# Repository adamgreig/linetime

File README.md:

# Linetime

Measure the line time. As precisely and accurately as feasible.

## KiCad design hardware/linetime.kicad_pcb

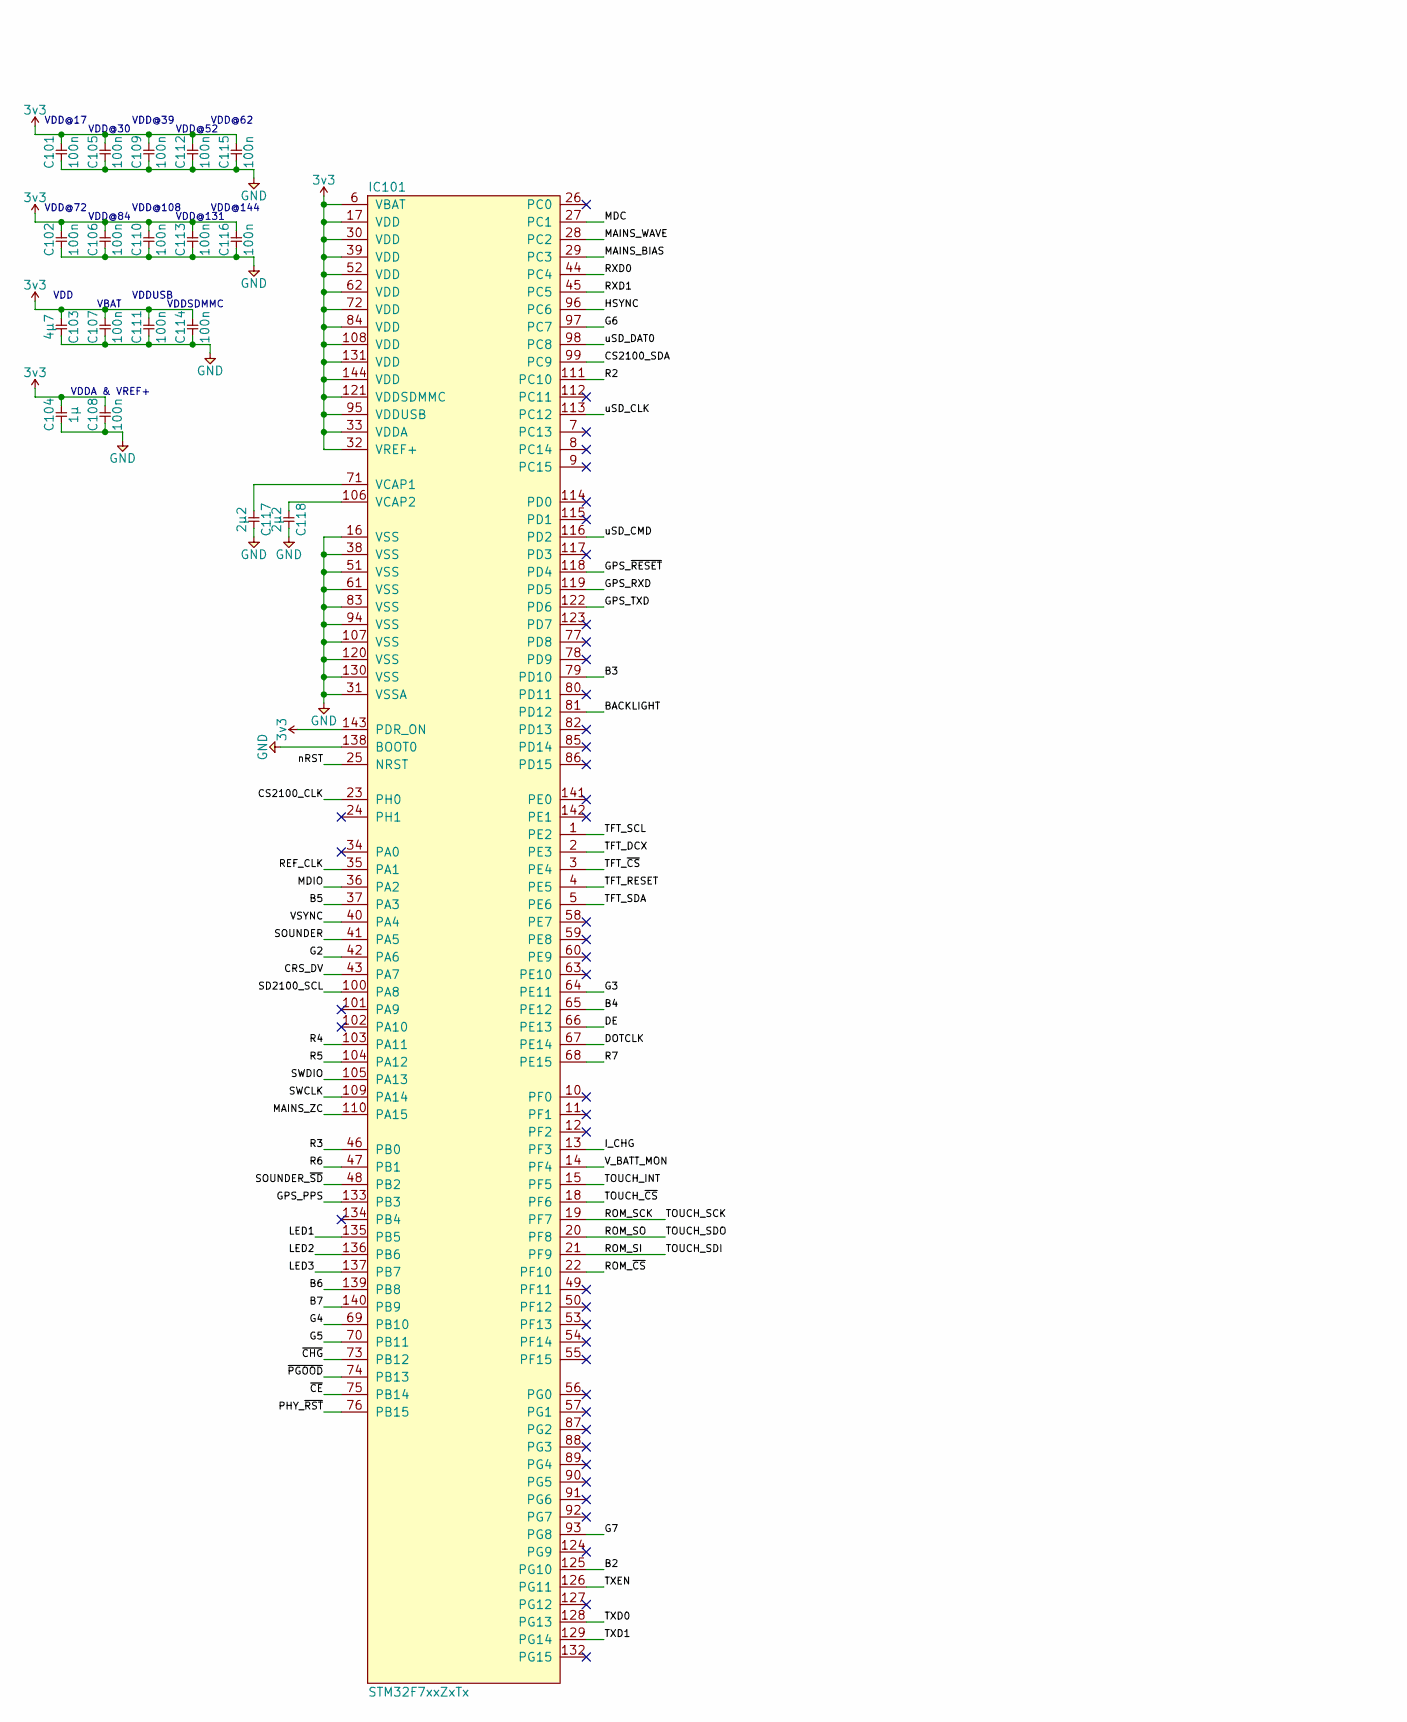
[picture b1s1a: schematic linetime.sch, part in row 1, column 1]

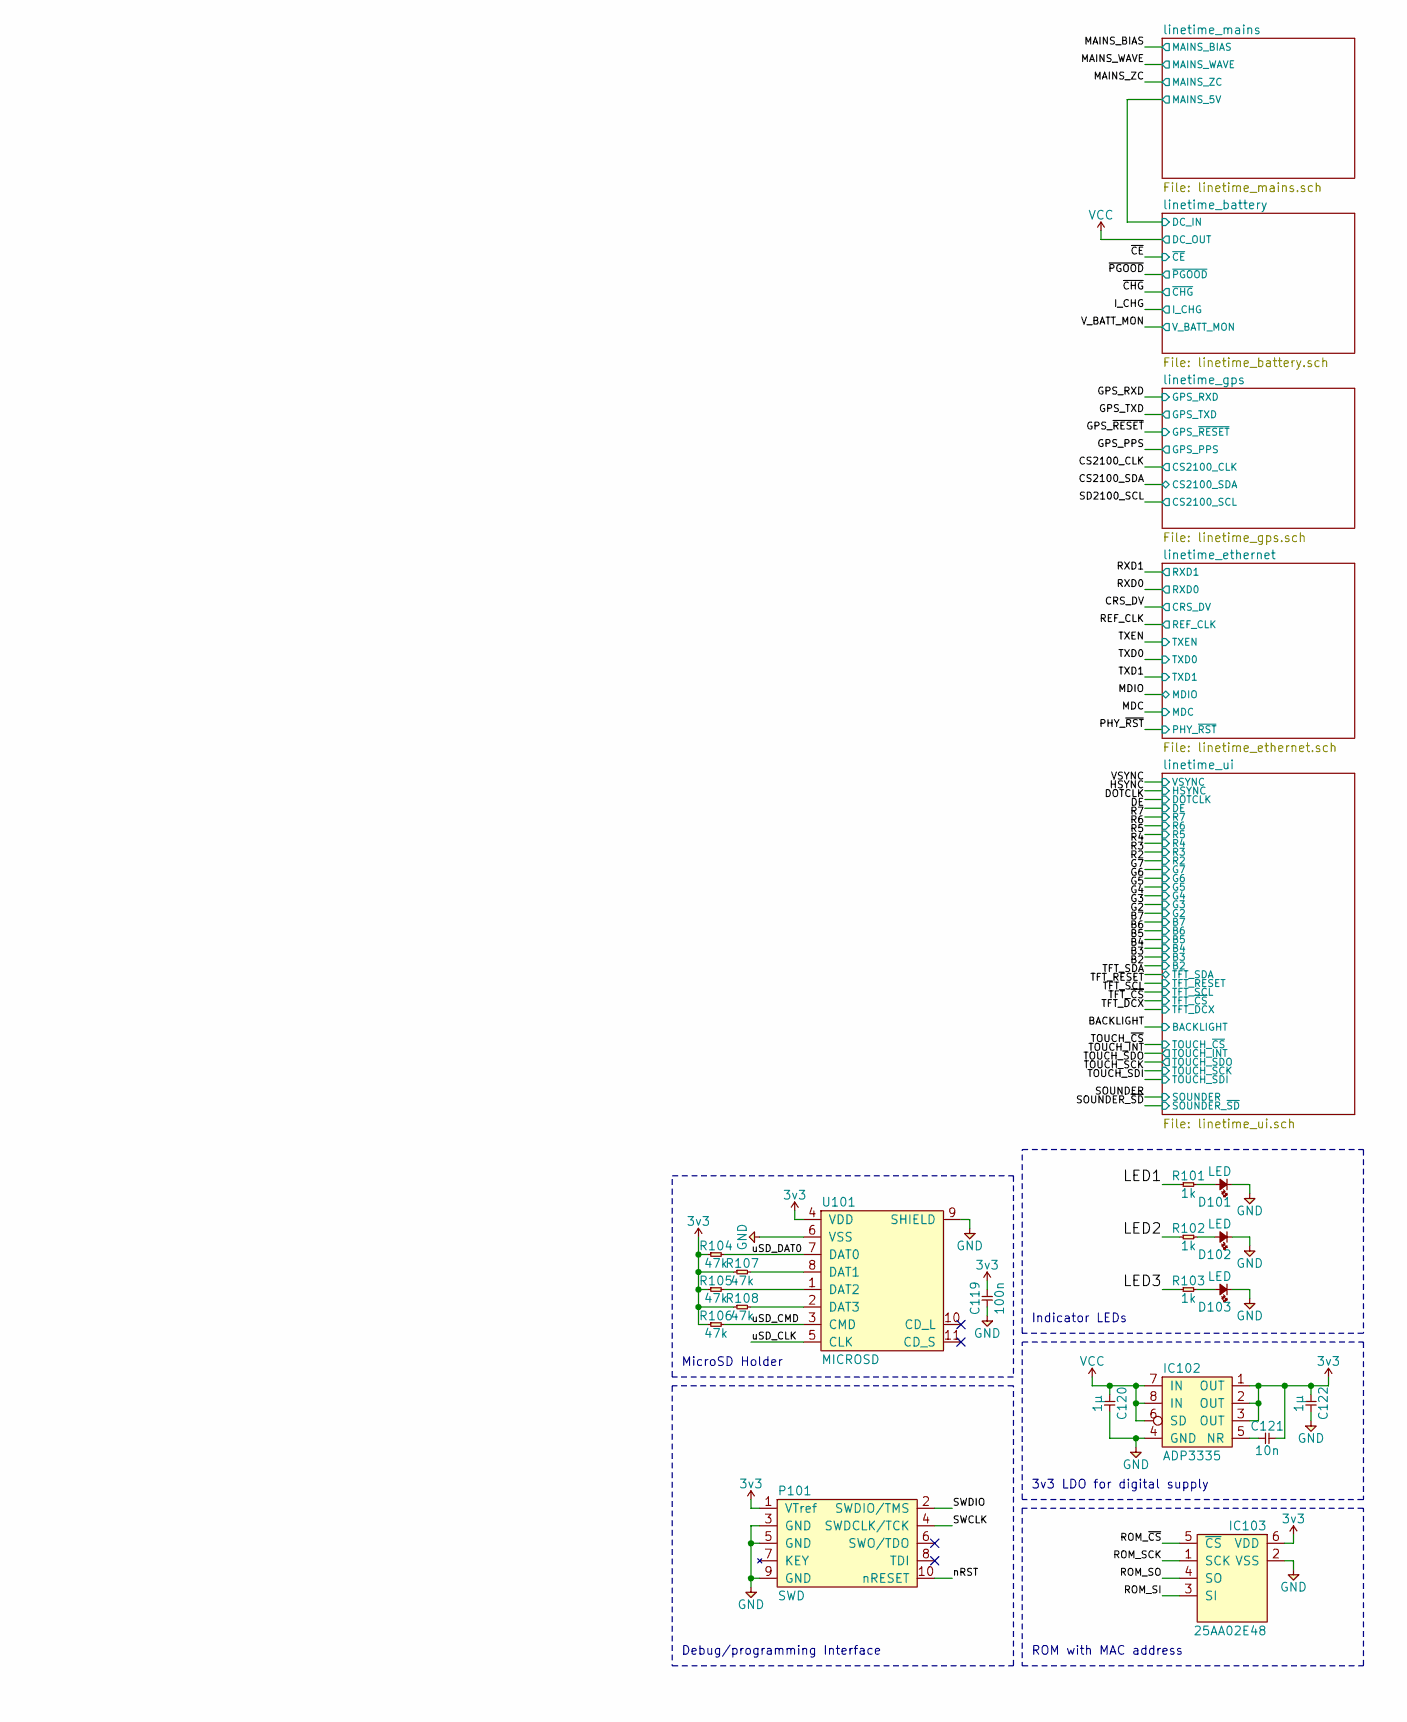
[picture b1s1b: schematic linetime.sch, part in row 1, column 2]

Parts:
C101, C102, C105, C106, C107, C108, C109, C110, C111, C112, C113, C114, C115, C116, C119: 100n; 0603
C103: 4µ7; 0603
C104, C120, C122: 1µ; 0603
C117, C118: 2µ2; 0603
C121: 10n; 0603
D101, D102, D103: LED; 0603-LED
IC101: STM32F7xxZxTx; LQFP-144; Farnell 2535499
IC102: ADP3335; MSOP-8; Farnell 2067775
IC103: 25AA02E48; SOT-23-6; Farnell 1700995
P101: SWD; FTSH-105-01-F-D-K
R101, R102, R103: 1k; 0603
R104, R105, R106, R107, R108: 47k; 0603
U101: MICROSD; MICROSD_MOLEX_503398-1892; Farnell 2358234

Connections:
3v3: C101.1, C102.1, C103.1, C104.1, C105.1, C106.1, C107.1, C108.1, C109.1, C110.1, C111.1, C112.1, C113.1, C114.1, C115.1, C116.1, C119.1, C121.2, C122.1, IC101.6 (VBAT), IC101.17 (VDD), IC101.30 (VDD), IC101.32 (VREF+), IC101.33 (VDDA), IC101.39 (VDD), IC101.52 (VDD), IC101.62 (VDD), IC101.72 (VDD), IC101.84 (VDD), IC101.95 (VDDUSB), IC101.108 (VDD), IC101.121 (VDDSDMMC), IC101.131 (VDD), IC101.143 (PDR_ON), IC101.144 (VDD), IC102.1 (OUT), IC102.2 (OUT), IC102.3 (OUT), IC103.6 (VDD), P101.1 (VTref), R104.1, R105.1, R106.1, R107.1, R108.1, U101.4 (VDD); also elsewhere on the board
/B2: IC101.125 (PG10); also elsewhere on the board
/B3: IC101.79 (PD10); also elsewhere on the board
/B4: IC101.65 (PE12); also elsewhere on the board
/B5: IC101.37 (PA3); also elsewhere on the board
/B6: IC101.139 (PB8); also elsewhere on the board
/B7: IC101.140 (PB9); also elsewhere on the board
/BACKLIGHT: IC101.81 (PD12); also elsewhere on the board
/CRS_DV: IC101.43 (PA7); also elsewhere on the board
/CS2100_CLK: IC101.23 (PH0); also elsewhere on the board
/CS2100_SDA: IC101.99 (PC9); also elsewhere on the board
/DE: IC101.66 (PE13); also elsewhere on the board
/DOTCLK: IC101.67 (PE14); also elsewhere on the board
/G2: IC101.42 (PA6); also elsewhere on the board
/G3: IC101.64 (PE11); also elsewhere on the board
/G4: IC101.69 (PB10); also elsewhere on the board
/G5: IC101.70 (PB11); also elsewhere on the board
/G6: IC101.97 (PC7); also elsewhere on the board
/G7: IC101.93 (PG8); also elsewhere on the board
/GPS_PPS: IC101.133 (PB3); also elsewhere on the board
/GPS_RXD: IC101.119 (PD5); also elsewhere on the board
/GPS_TXD: IC101.122 (PD6); also elsewhere on the board
/GPS_~RESET: IC101.118 (PD4); also elsewhere on the board
/HSYNC: IC101.96 (PC6); also elsewhere on the board
/I_CHG: IC101.13 (PF3); also elsewhere on the board
/LED1: IC101.135 (PB5), R101.1
/LED2: IC101.136 (PB6), R102.1
/LED3: IC101.137 (PB7), R103.1
/MAINS_BIAS: IC101.29 (PC3); also elsewhere on the board
/MAINS_WAVE: IC101.28 (PC2); also elsewhere on the board
/MAINS_ZC: IC101.110 (PA15); also elsewhere on the board
/MDC: IC101.27 (PC1); also elsewhere on the board
/MDIO: IC101.36 (PA2); also elsewhere on the board
/PHY_~RST: IC101.76 (PB15); also elsewhere on the board
/R2: IC101.111 (PC10); also elsewhere on the board
/R3: IC101.46 (PB0); also elsewhere on the board
/R4: IC101.103 (PA11); also elsewhere on the board
/R5: IC101.104 (PA12); also elsewhere on the board
/R6: IC101.47 (PB1); also elsewhere on the board
/R7: IC101.68 (PE15); also elsewhere on the board
/REF_CLK: IC101.35 (PA1); also elsewhere on the board
/ROM_SCK: IC101.19 (PF7), IC103.1 (SCK); also elsewhere on the board
/ROM_SI: IC101.21 (PF9), IC103.3 (SI); also elsewhere on the board
/ROM_SO: IC101.20 (PF8), IC103.4 (SO); also elsewhere on the board
/ROM_~CS: IC101.22 (PF10), IC103.5 (~CS)
/RXD0: IC101.44 (PC4); also elsewhere on the board
/RXD1: IC101.45 (PC5); also elsewhere on the board
/SD2100_SCL: IC101.100 (PA8); also elsewhere on the board
/SOUNDER: IC101.41 (PA5); also elsewhere on the board
/SOUNDER_~SD: IC101.48 (PB2); also elsewhere on the board
/SWCLK: IC101.109 (PA14), P101.4 (SWDCLK/TCK)
/SWDIO: IC101.105 (PA13), P101.2 (SWDIO/TMS)
/TFT_DCX: IC101.2 (PE3); also elsewhere on the board
/TFT_RESET: IC101.4 (PE5); also elsewhere on the board
/TFT_SCL: IC101.1 (PE2); also elsewhere on the board
/TFT_SDA: IC101.5 (PE6); also elsewhere on the board
/TFT_~CS: IC101.3 (PE4); also elsewhere on the board
/TOUCH_INT: IC101.15 (PF5); also elsewhere on the board
/TOUCH_~CS: IC101.18 (PF6); also elsewhere on the board
/TXD0: IC101.128 (PG13); also elsewhere on the board
/TXD1: IC101.129 (PG14); also elsewhere on the board
/TXEN: IC101.126 (PG11); also elsewhere on the board
/VSYNC: IC101.40 (PA4); also elsewhere on the board
/V_BATT_MON: IC101.14 (PF4); also elsewhere on the board
/nRST: IC101.25 (NRST), P101.10 (nRESET)
/uSD_CLK: IC101.113 (PC12), U101.5 (CLK)
/uSD_CMD: IC101.116 (PD2), R106.2, U101.3 (CMD)
/uSD_DAT0: IC101.98 (PC8), R104.2, U101.7 (DAT0)
/~CE: IC101.75 (PB14); also elsewhere on the board
/~CHG: IC101.73 (PB12); also elsewhere on the board
/~PGOOD: IC101.74 (PB13); also elsewhere on the board
GND: C101.2, C102.2, C103.2, C104.2, C105.2, C106.2, C107.2, C108.2, C109.2, C110.2, C111.2, C112.2, C113.2, C114.2, C115.2, C116.2, C117.2, C118.2, C119.2, C120.2, C122.2, D101.1, D102.1, D103.1, IC101.16 (VSS), IC101.31 (VSSA), IC101.38 (VSS), IC101.51 (VSS), IC101.61 (VSS), IC101.83 (VSS), IC101.94 (VSS), IC101.107 (VSS), IC101.120 (VSS), IC101.130 (VSS), IC101.138 (BOOT0), IC102.4 (GND), IC103.2 (VSS), P101.3 (GND), P101.5 (GND), P101.9 (GND), U101.6 (VSS), U101.9 (SHIELD); also elsewhere on the board
unnamed: C117.1, IC101.71 (VCAP1)
unnamed: C118.1, IC101.106 (VCAP2)
unnamed: C121.1, IC102.5 (NR)
unnamed: D101.2, R101.2
unnamed: D102.2, R102.2
unnamed: D103.2, R103.2
unnamed: R105.2, U101.1 (DAT2)
unnamed: R107.2, U101.8 (DAT1)
unnamed: R108.2, U101.2 (DAT3)
VCC: C120.1, IC102.6 (SD), IC102.7 (IN), IC102.8 (IN); also elsewhere on the board

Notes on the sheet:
3v3 LDO for digital supply
ROM with MAC address
MicroSD Holder
Debug/programming Interface
VDDA & VREF+
VDDUSB
VDDSDMMC
VBAT
VDD
VDD@17
VDD@30
VDD@39
VDD@52
VDD@62
VDD@72
VDD@84
VDD@108
VDD@131
VDD@144
Indicator LEDs

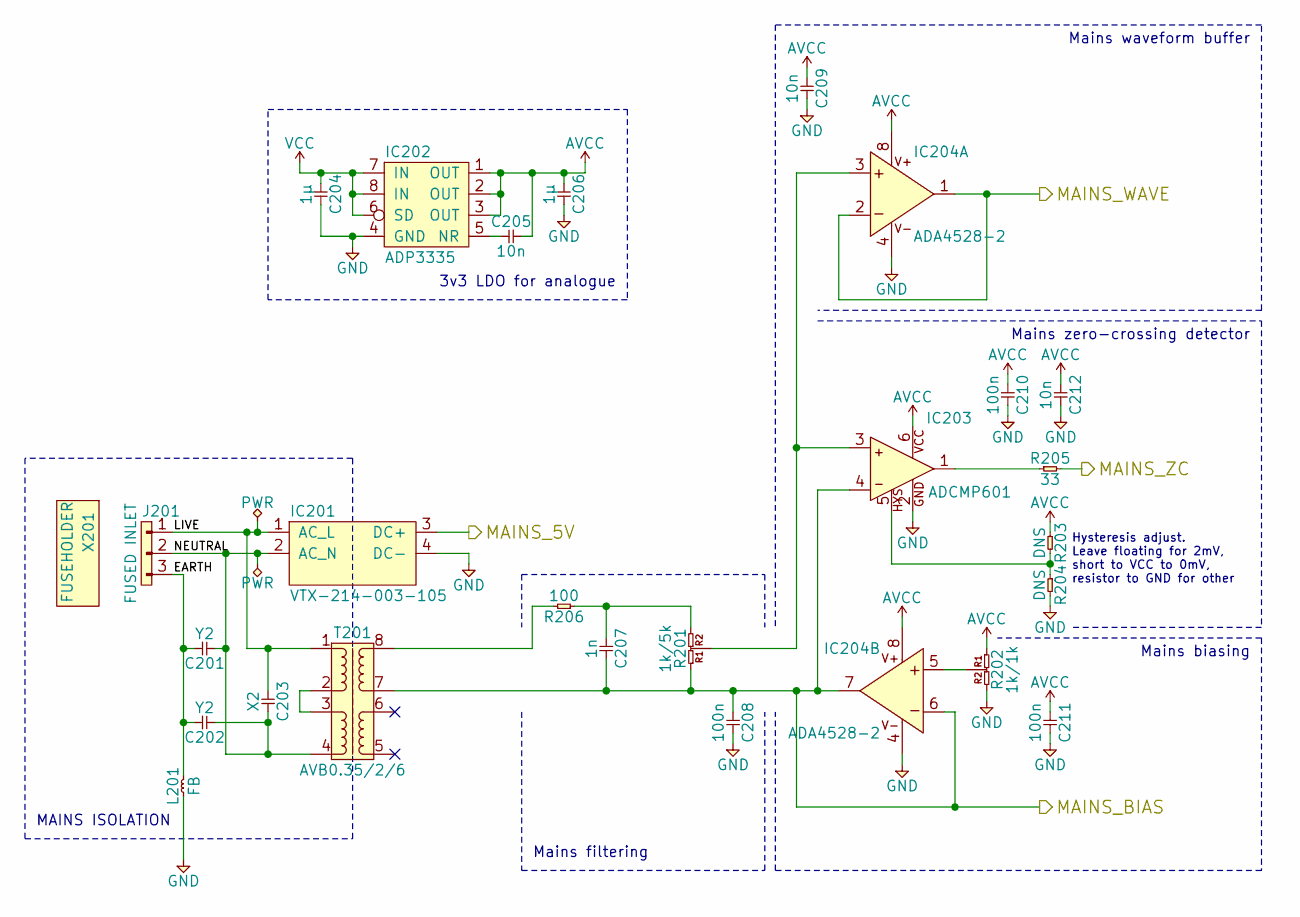
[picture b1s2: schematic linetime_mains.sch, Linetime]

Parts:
C201, C202: Y2; B32921; Farnell 2395807
C203: X2; B32921; Farnell 2112770
C204, C206: 1µ; 0603
C205, C209, C212: 10n; 0603
C207: 1n; 0603
C208, C210, C211: 100n; 0603
IC201: VTX-214-003-105; VTX-214-003-1xx; Farnell 2401030
IC202: ADP3335; MSOP-8; Farnell 2067775
IC203: ADCMP601; SC-70-6; Farnell 1331025
IC204: ADA4528-2; MSOP-8; Farnell 2213573
J201: FUSED INLET; DD21.01xx.1111; Farnell 1517985
L201: FB; 0603; Farnell 1669708
R201: 1k/5k; SOT-23; Farnell 2325454
R202: 1k/1k; SOT-23; Farnell 1203390
R203, R204: DNS; 0603
R205: 33; 0603
R206: 100; 0603
T201: AVB0.35/2/6; AVB0.35_2_X; Farnell 1131455
X201: FUSEHOLDER; Farnell 1144906

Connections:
/MAINS_BIAS: C207.2, C208.1, IC203.4 (-), IC204.6 (-), IC204.7 (OUT), R201.1, T201.7; also elsewhere on the board
/MAINS_WAVE: IC204.1 (OUT), IC204.2 (-); also elsewhere on the board
/MAINS_ZC: R205.2; also elsewhere on the board
/linetime_battery/DC_IN: IC201.3 (DC+); also elsewhere on the board
/linetime_mains/EARTH: C201.2, C202.2, J201.3, L201.2
/linetime_mains/LIVE: C203.1, IC201.1 (AC_L), J201.1, T201.1
/linetime_mains/NEUTRAL: C201.1, C202.1, C203.2, IC201.2 (AC_N), J201.2, T201.4
AVCC: C205.2, C206.1, C209.1, C210.1, C211.1, C212.1, IC202.1 (OUT), IC202.2 (OUT), IC202.3 (OUT), IC203.6 (VCC), IC204.8 (V+), R202.1, R203.1
GND: C204.2, C206.2, C208.2, C209.2, C210.2, C211.2, C212.2, IC201.4 (DC-), IC202.4 (GND), IC203.2 (GND), IC204.4 (V-), L201.1, R202.2, R204.2; also elsewhere on the board
unnamed: C205.1, IC202.5 (NR)
unnamed: C207.1, R201.2, R206.1
unnamed: IC203.1 (Q), R205.1
unnamed: IC203.3 (+), IC204.3 (+), R201.3
unnamed: IC203.5 (LE/HYS), R203.2, R204.1
unnamed: IC204.5 (+), R202.3
unnamed: R206.2, T201.8
unnamed: T201.2, T201.3
VCC: C204.1, IC202.6 (SD), IC202.7 (IN), IC202.8 (IN); also elsewhere on the board

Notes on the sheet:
MAINS ISOLATION
Hysteresis adjust. Leave floating for 2mV, short to VCC to 0mV, resistor to GND for other
Mains waveform buffer
Mains zero-crossing detector
Mains biasing
Mains filtering
3v3 LDO for analogue

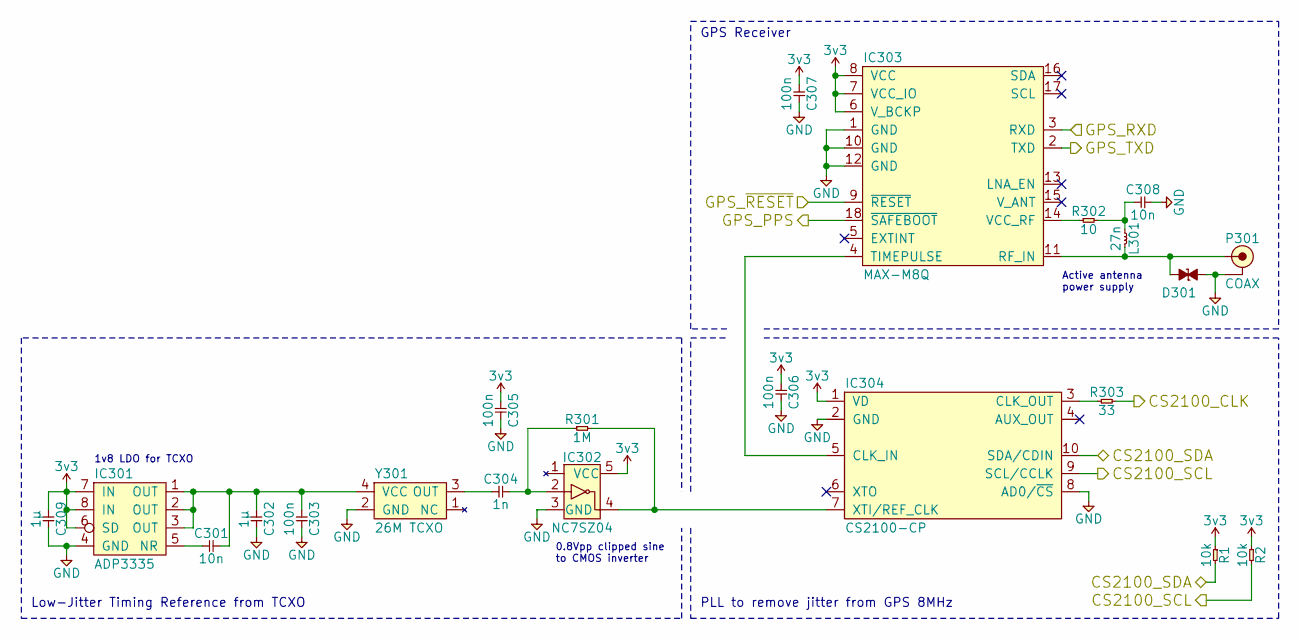
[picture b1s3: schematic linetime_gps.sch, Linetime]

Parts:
C301, C308: 10n; 0603
C302, C309: 1µ; 0603
C303, C305, C306, C307: 100n; 0603
C304: 1n; 0603
D301: ESD_DIODE; 0402; Farnell 2368169
IC301: ADP3335; MSOP-8; Farnell 2376932
IC302: NC7SZ04; SOT-23-5; Farnell 1417667
IC303: MAX-M8Q
IC304: CS2100-CP; MSOP-10; Mouser 777-CS2100CP-CZZ
L301: 27n; 0603
P301: COAX; SMA-PTH; Farnell 2112448
R1, R2: 10k; 0603
R301: 1M; 0603
R302: 10; 0603
R303: 33; 0603
Y301: 26M TCXO; TG-5006CG; Farnell 2405785

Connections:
3v3: C305.1, C306.1, C307.1, C309.1, IC301.6 (SD), IC301.7 (IN), IC301.8 (IN), IC302.5 (VCC), IC303.6 (V_BCKP), IC303.7 (VCC_IO), IC303.8 (VCC), IC304.1 (VD), R1.1, R2.1; also elsewhere on the board
/CS2100_CLK: R303.2; also elsewhere on the board
/CS2100_SDA: IC304.10 (SDA/CDIN), R1.2; also elsewhere on the board
/GPS_PPS: IC303.18 (~SAFEBOOT); also elsewhere on the board
/GPS_RXD: IC303.3 (RXD); also elsewhere on the board
/GPS_TXD: IC303.2 (TXD); also elsewhere on the board
/GPS_~RESET: IC303.9 (~RESET); also elsewhere on the board
/SD2100_SCL: IC304.9 (SCL/CCLK), R2.2; also elsewhere on the board
GND: C302.2, C303.2, C305.2, C306.2, C307.2, C308.2, C309.2, D301.1, IC301.4 (GND), IC302.3 (GND), IC303.1 (GND), IC303.10 (GND), IC303.12 (GND), IC304.2 (GND), IC304.8 (AD0/~CS), P301.2 (GND), Y301.2 (GND); also elsewhere on the board
unnamed: C301.1, IC301.5 (NR)
unnamed: C301.2, C302.1, C303.1, IC301.1 (OUT), IC301.2 (OUT), IC301.3 (OUT), Y301.4 (VCC)
unnamed: C304.1, Y301.3 (OUT)
unnamed: C304.2, IC302.2, R301.1
unnamed: C308.1, L301.1, R302.2
unnamed: D301.2, IC303.11 (RF_IN), L301.2, P301.1 (RF)
unnamed: IC302.4, IC304.7 (XTI/REF_CLK), R301.2
unnamed: IC303.4 (TIMEPULSE), IC304.5 (CLK_IN)
unnamed: IC303.14 (VCC_RF), R302.1
unnamed: IC304.3 (CLK_OUT), R303.1

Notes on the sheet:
1v8 LDO for TCXO
0.8Vpp clipped sine to CMOS inverter
Low-Jitter Timing Reference from TCXO
PLL to remove jitter from GPS 8MHz
GPS Receiver
Active antenna power supply

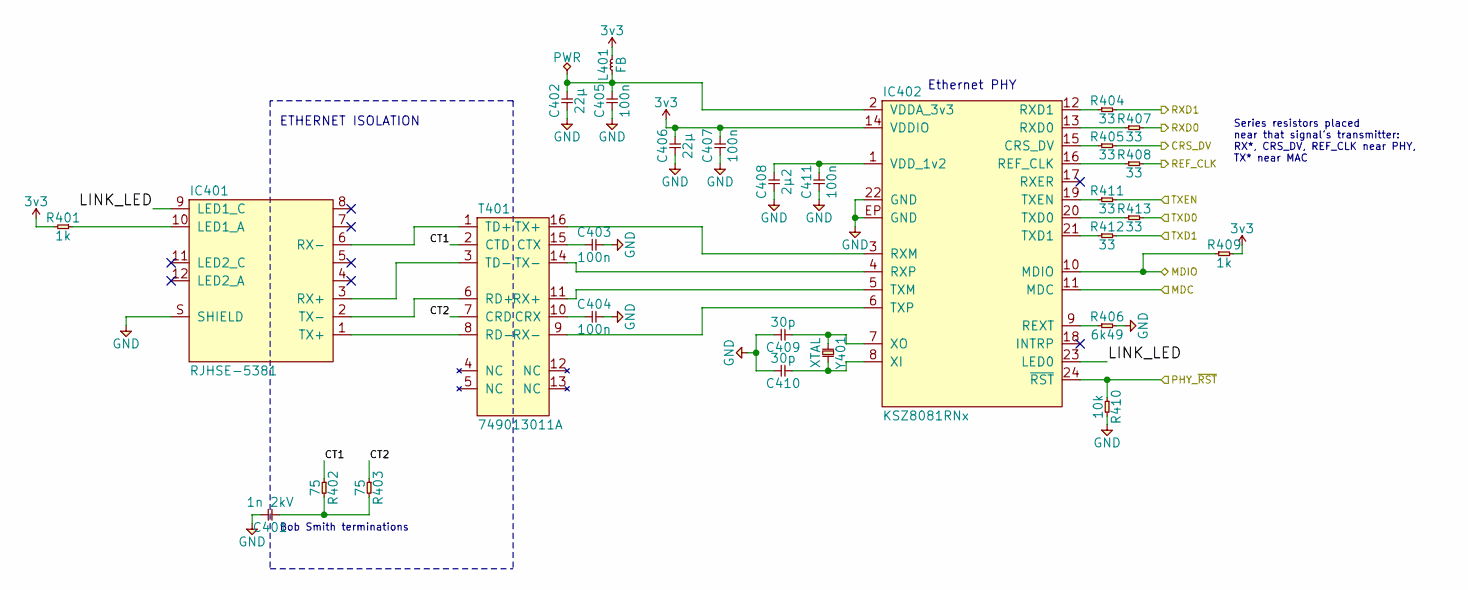
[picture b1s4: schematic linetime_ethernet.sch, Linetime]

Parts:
C401: 1n 2kV; 1206; Farnell 1855909
C402, C406: 22µ; 0603
C403, C404, C405, C407, C411: 100n; 0603
C408: 2µ2; 0603
C409, C410: 30p; 0603
IC401: RJHSE-5381; RJHSE-538X; Farnell 1462758
IC402: KSZ8081RNx; QFN-24-EP-MICREL; Farnell 2509802
L401: FB; 0603; Farnell 1669708
R401, R409: 1k; 0603
R402, R403: 75; 0603; Farnell 2059571
R404, R405, R407, R408, R411, R412, R413: 33; 0603
R406: 6k49; 0603
R410: 10k; 0603
T401: 749013011A; 749010012A; Farnell 2422553
Y401: XTAL; XTAL-50x32; Farnell 2101328

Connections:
3v3: C406.2, C407.2, IC402.14 (VDDIO), L401.2, R401.2, R409.2; also elsewhere on the board
/CRS_DV: R405.2; also elsewhere on the board
/MDC: IC402.11 (MDC); also elsewhere on the board
/MDIO: IC402.10 (MDIO), R409.1; also elsewhere on the board
/PHY_~RST: IC402.24 (~RST), R410.1; also elsewhere on the board
/REF_CLK: R408.2; also elsewhere on the board
/RXD0: R407.2; also elsewhere on the board
/RXD1: R404.2; also elsewhere on the board
/TXD0: R413.2; also elsewhere on the board
/TXD1: R412.2; also elsewhere on the board
/TXEN: R411.2; also elsewhere on the board
/linetime_ethernet/CT1: R402.1, T401.2 (CTD)
/linetime_ethernet/CT2: R403.1, T401.7 (CRD)
/linetime_ethernet/LINK_LED: IC401.9 (LED1_C), IC402.23 (LED0)
GND: C401.2, C402.1, C403.2, C404.2, C405.1, C406.1, C407.1, C408.1, C409.2, C410.2, C411.1, IC401.S (SHIELD), IC402.22 (GND), IC402.EP (GND), R406.2, R410.2; also elsewhere on the board
unnamed: C401.1, R402.2, R403.2
unnamed: C402.2, C405.2, IC402.2 (VDDA_3v3), L401.1
unnamed: C403.1, T401.15 (CTX)
unnamed: C404.1, T401.10 (CRX)
unnamed: C408.2, C411.2, IC402.1 (VDD_1v2)
unnamed: C409.1, IC402.7 (XO), Y401.1
unnamed: C410.1, IC402.8 (XI), Y401.2
unnamed: IC401.1 (TX+), T401.8 (RD-)
unnamed: IC401.2 (TX-), T401.6 (RD+)
unnamed: IC401.3 (RX+), T401.3 (TD-)
unnamed: IC401.6 (RX-), T401.1 (TD+)
unnamed: IC401.10 (LED1_A), R401.1
unnamed: IC402.3 (RXM), T401.16 (TX+)
unnamed: IC402.4 (RXP), T401.14 (TX-)
unnamed: IC402.5 (TXM), T401.11 (RX+)
unnamed: IC402.6 (TXP), T401.9 (RX-)
unnamed: IC402.9 (REXT), R406.1
unnamed: IC402.12 (RXD1), R404.1
unnamed: IC402.13 (RXD0), R407.1
unnamed: IC402.15 (CRS_DV), R405.1
unnamed: IC402.16 (REF_CLK), R408.1
unnamed: IC402.19 (TXEN), R411.1
unnamed: IC402.20 (TXD0), R413.1
unnamed: IC402.21 (TXD1), R412.1

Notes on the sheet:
Bob Smith terminations
ETHERNET ISOLATION
Ethernet PHY
Series resistors placed near that signal's transmitter: RX*, CRS_DV, REF_CLK near PHY, TX* near MAC

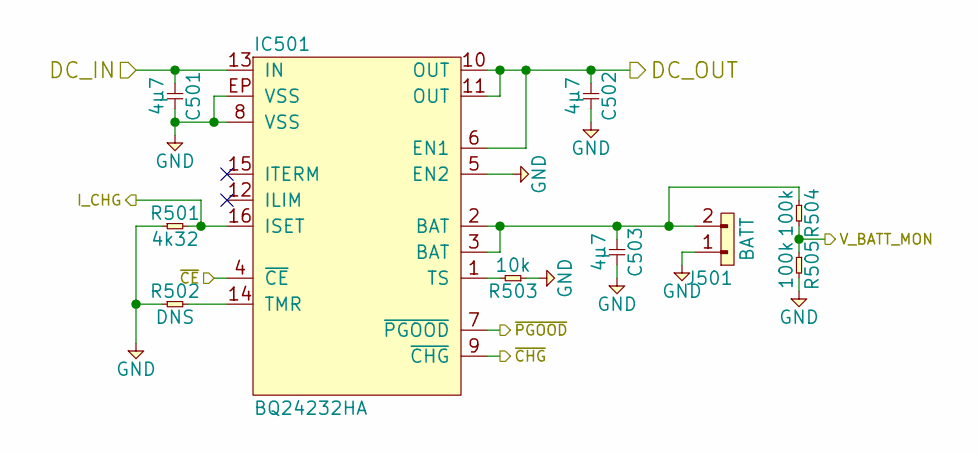
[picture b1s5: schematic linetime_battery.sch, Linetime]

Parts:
C501, C502, C503: 4µ7; 0603
IC501: BQ24232HA; QFN-16-EP-TI; Farnell 2576286
J501: BATT; S02B-PASK-2
R501: 4k32; 0603
R502: DNS; 0603
R503: 10k; 0603
R504, R505: 100k; 0603

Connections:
/I_CHG: IC501.16 (ISET), R501.2; also elsewhere on the board
/V_BATT_MON: R504.2, R505.1; also elsewhere on the board
/linetime_battery/DC_IN: C501.1, IC501.13 (IN); also elsewhere on the board
/~CE: IC501.4 (~CE); also elsewhere on the board
/~CHG: IC501.9 (~CHG); also elsewhere on the board
/~PGOOD: IC501.7 (~PGOOD); also elsewhere on the board
GND: C501.2, C502.2, C503.2, IC501.5 (EN2), IC501.8 (VSS), IC501.EP (VSS), J501.1, R501.1, R502.1, R503.1, R505.2; also elsewhere on the board
unnamed: C503.1, IC501.2 (BAT), IC501.3 (BAT), J501.2, R504.1
unnamed: IC501.1 (TS), R503.2
unnamed: IC501.14 (TMR), R502.2
VCC: C502.1, IC501.6 (EN1), IC501.10 (OUT), IC501.11 (OUT); also elsewhere on the board

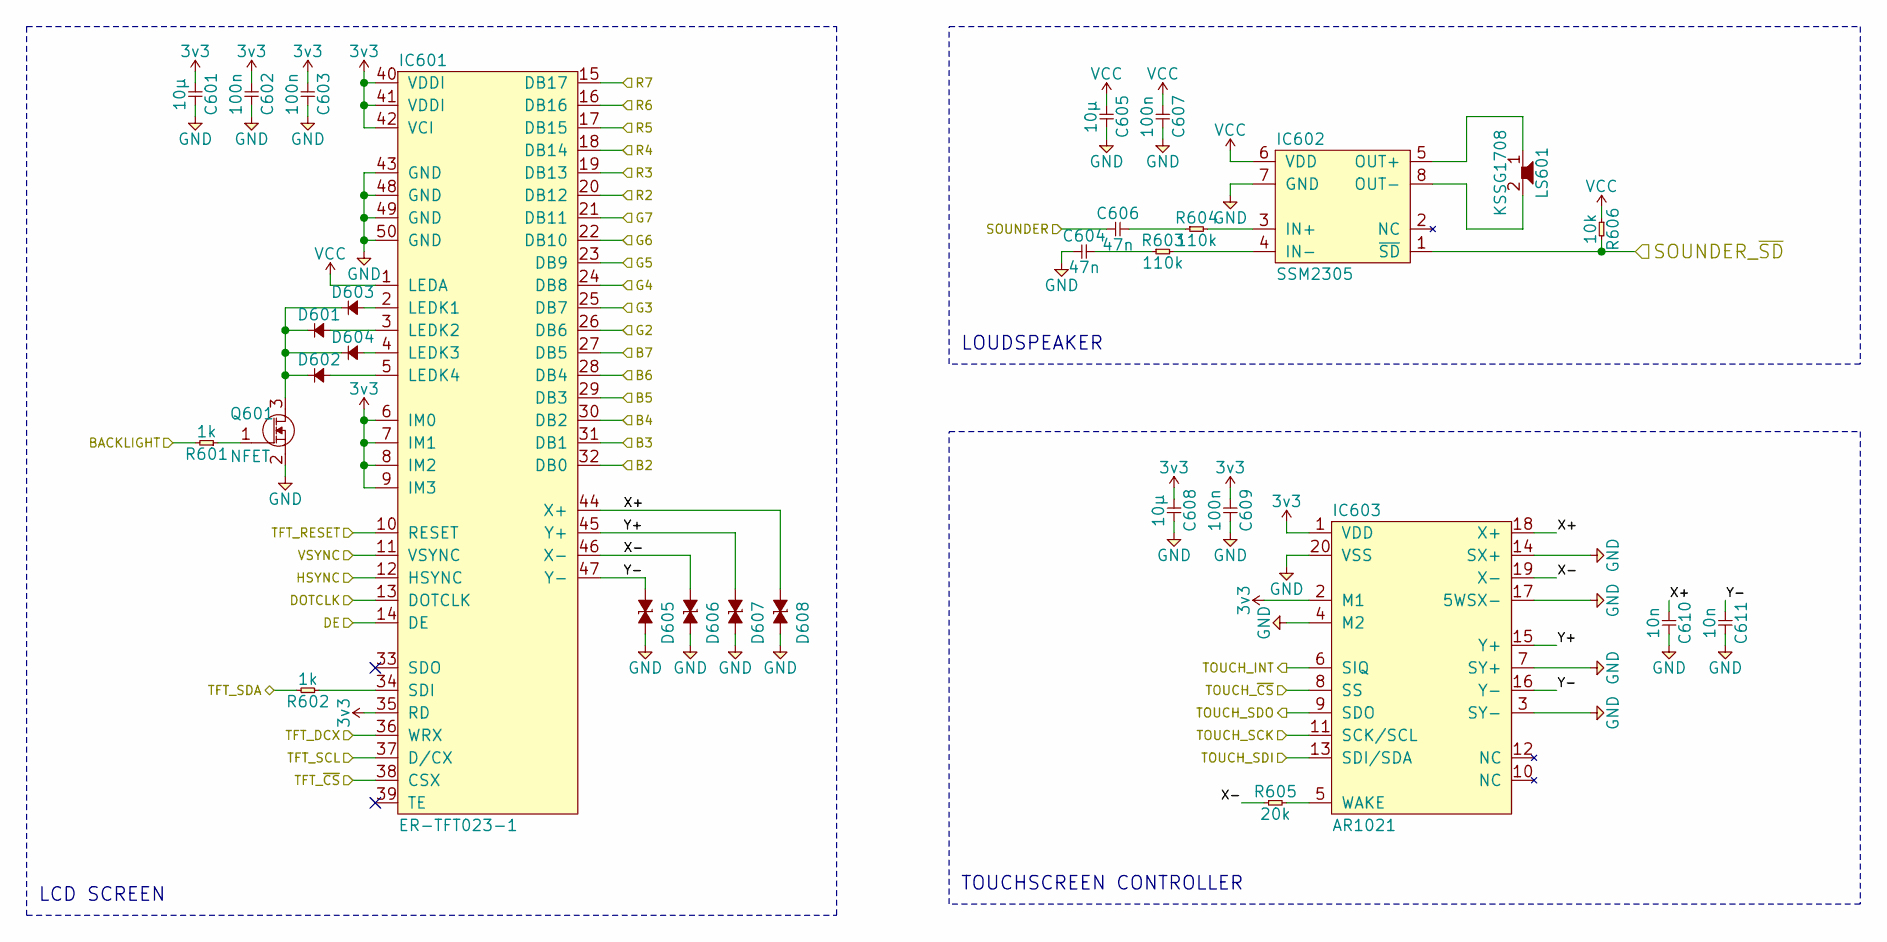
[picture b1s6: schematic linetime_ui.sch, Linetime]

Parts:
C601, C605, C608: 10µ; 0603
C602, C603, C607, C609: 100n; 0603
C604, C606: 47n; 0603
C610, C611: 10n; 0603
D601, D602, D603, D604: SOD-123; Farnell 1794973
D605, D606, D607, D608: ESD_DIODE; 0402; Farnell 2368169
IC601: ER-TFT023-1; ER-CON50HT-1
IC602: SSM2305; MSOP-8; Farnell 2074853
IC603: AR1021; SSOP-20; Farnell 2218568
LS601: KSSG1708; Farnell 1502738
Q601: NFET; SOT-23; Farnell 2069541
R601, R602: 1k; 0603
R603, R604: 110k; 0603
R605: 20k; 0603
R606: 10k; 0603

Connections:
3v3: C601.1, C602.1, C603.1, C608.1, C609.1, IC601.6 (IM0), IC601.7 (IM1), IC601.8 (IM2), IC601.9 (IM3), IC601.35 (RD), IC601.40 (VDDI), IC601.41 (VDDI), IC601.42 (VCI), IC603.1 (VDD), IC603.2 (M1); also elsewhere on the board
/B2: IC601.32 (DB0); also elsewhere on the board
/B3: IC601.31 (DB1); also elsewhere on the board
/B4: IC601.30 (DB2); also elsewhere on the board
/B5: IC601.29 (DB3); also elsewhere on the board
/B6: IC601.28 (DB4); also elsewhere on the board
/B7: IC601.27 (DB5); also elsewhere on the board
/BACKLIGHT: R601.2; also elsewhere on the board
/DE: IC601.14 (DE); also elsewhere on the board
/DOTCLK: IC601.13 (DOTCLK); also elsewhere on the board
/G2: IC601.26 (DB6); also elsewhere on the board
/G3: IC601.25 (DB7); also elsewhere on the board
/G4: IC601.24 (DB8); also elsewhere on the board
/G5: IC601.23 (DB9); also elsewhere on the board
/G6: IC601.22 (DB10); also elsewhere on the board
/G7: IC601.21 (DB11); also elsewhere on the board
/HSYNC: IC601.12 (HSYNC); also elsewhere on the board
/R2: IC601.20 (DB12); also elsewhere on the board
/R3: IC601.19 (DB13); also elsewhere on the board
/R4: IC601.18 (DB14); also elsewhere on the board
/R5: IC601.17 (DB15); also elsewhere on the board
/R6: IC601.16 (DB16); also elsewhere on the board
/R7: IC601.15 (DB17); also elsewhere on the board
/ROM_SCK: IC603.11 (SCK/SCL); also elsewhere on the board
/ROM_SI: IC603.13 (SDI/SDA); also elsewhere on the board
/ROM_SO: IC603.9 (SDO); also elsewhere on the board
/SOUNDER: C606.1; also elsewhere on the board
/SOUNDER_~SD: IC602.1 (~SD), R606.2; also elsewhere on the board
/TFT_DCX: IC601.36 (WRX); also elsewhere on the board
/TFT_RESET: IC601.10 (RESET); also elsewhere on the board
/TFT_SCL: IC601.37 (D/CX); also elsewhere on the board
/TFT_SDA: R602.2; also elsewhere on the board
/TFT_~CS: IC601.38 (CSX); also elsewhere on the board
/TOUCH_INT: IC603.6 (SIQ); also elsewhere on the board
/TOUCH_~CS: IC603.8 (SS); also elsewhere on the board
/VSYNC: IC601.11 (VSYNC); also elsewhere on the board
/linetime_ui/X+: C610.1, D608.1, IC601.44 (X+), IC603.18 (X+)
/linetime_ui/X-: D606.1, IC601.46 (X-), IC603.19 (X-), R605.1
/linetime_ui/Y+: D607.1, IC601.45 (Y+), IC603.15 (Y+)
/linetime_ui/Y-: C611.1, D605.1, IC601.47 (Y-), IC603.16 (Y-)
GND: C601.2, C602.2, C603.2, C604.1, C605.2, C607.2, C608.2, C609.2, C610.2, C611.2, D605.2, D606.2, D607.2, D608.2, IC601.43 (GND), IC601.48 (GND), IC601.49 (GND), IC601.50 (GND), IC602.7 (GND), IC603.3 (SY-), IC603.4 (M2), IC603.7 (SY+), IC603.14 (SX+), IC603.17 (5WSX-), IC603.20 (VSS), Q601.2 (S); also elsewhere on the board
unnamed: C604.2, R603.1
unnamed: C606.2, R604.1
unnamed: D601.1, D602.1, D603.1, D604.1, Q601.3 (D)
unnamed: D601.2, IC601.3 (LEDK2)
unnamed: D602.2, IC601.5 (LEDK4)
unnamed: D603.2, IC601.2 (LEDK1)
unnamed: D604.2, IC601.4 (LEDK3)
unnamed: IC601.34 (SDI), R602.1
unnamed: IC602.3 (IN+), R604.2
unnamed: IC602.4 (IN-), R603.2
unnamed: IC602.5 (OUT+), LS601.1
unnamed: IC602.8 (OUT-), LS601.2
unnamed: IC603.5 (WAKE), R605.2
unnamed: Q601.1 (G), R601.1
VCC: C605.1, C607.1, IC601.1 (LEDA), IC602.6 (VDD), R606.1; also elsewhere on the board

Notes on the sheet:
LOUDSPEAKER
LCD SCREEN
TOUCHSCREEN CONTROLLER
